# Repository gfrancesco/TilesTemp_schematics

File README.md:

# TilesTemp electronic schematics

In this repository are contained the Eagle schematic files for the TilesTemp temperature and humidity sensor.

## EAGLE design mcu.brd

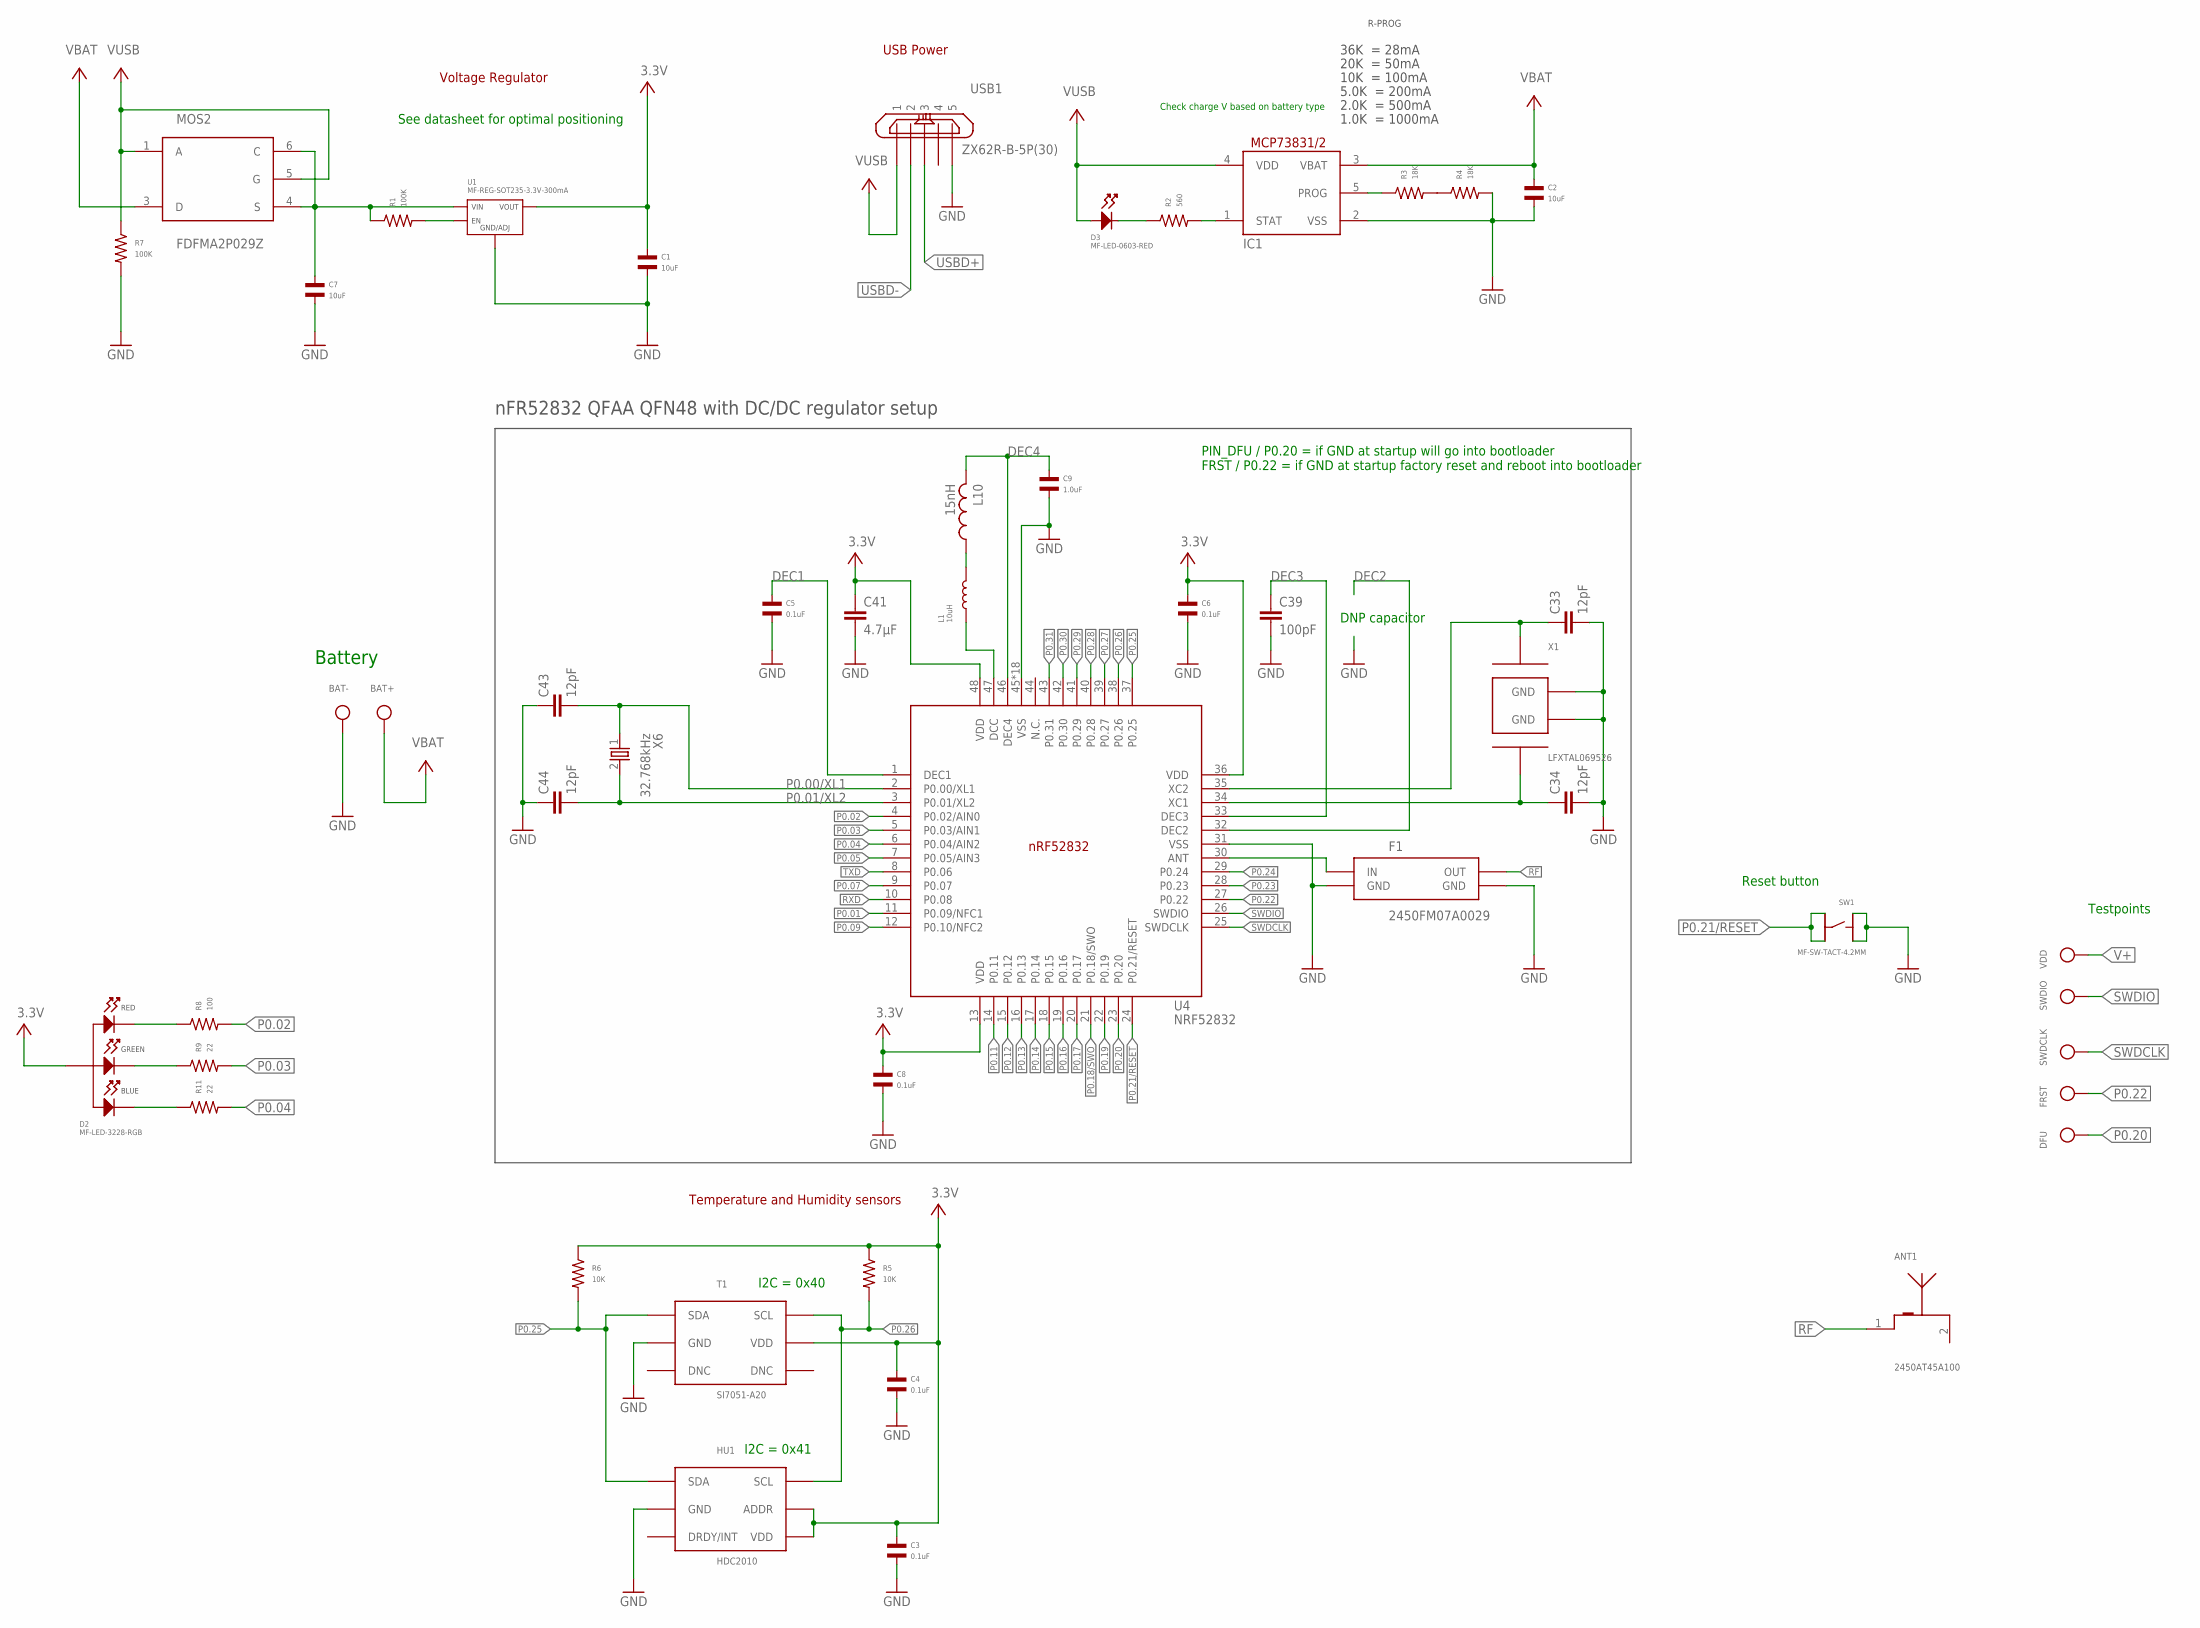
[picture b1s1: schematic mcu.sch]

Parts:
ANT1: 2450AT45A100; MPN 2450AT45A100E
BAT+: TESTPOINTROUND2MM; TESTPOINT_ROUND_2MM
BAT-: TESTPOINTROUND2MM; TESTPOINT_ROUND_2MM
C1, C2, C7: 10uF; C0603; MPN JMK107ABJ106KA-T
C3, C4, C5, C6, C8: 0.1uF; C0402; MPN MF-CAP-0402-0.1uF
C9: 1.0uF; C0603; MPN MF-CAP-0603-1uF
C33, C34, C43, C44: 12pF; RESC0402_N; MPN C0402C120J5GACTU
C39: 100pF; RESC0402_N; MPN GRM1555C1H101GA01D
C41: 4.7µF; RESC0603_N; MPN 06036D475KAT2A
D2: MF-LED-3228-RGB; PLCC4
D3: MF-LED-0603-RED; LED0603
DFU: TESTPOINTROUND2MM; TESTPOINT_ROUND_2MM
F1: 2450FM07A0029; 0402_RF; MPN 2450FM07A0029T
FRST: TESTPOINTROUND2MM; TESTPOINT_ROUND_2MM
HU1: HDC2010; DSBGA-6; MPN HDC2010YPAR
IC1: MCP73831/OT; SOT23-5L; MPN MCP73831T-2ACI/OT
L1: 10uH; L1210; MPN MF-IND-1210-10uH
L10: 15nH; RESC0402_N; MPN L-07C15NJV6T
MOS2: FDFMA2P029Z; MICROFET_2X2; MPN FDFMA2P029Z
R1, R7: 100K; R0402; MPN MF-RES-0402-100K
R2: 560; R0402; MPN MF-RES-0402-560
R3, R4: 18K; R0402; MPN MF-RES-0402-18K
R5, R6: 10K; R0402; MPN MF-RES-0402-10K
R8: 100; R0402; MPN MF-RES-0402-100
R9, R11: 22; R0402; MPN MF-RES-0402-22
SW1: MF-SW-TACT-4.2MM; TACT4.2MM
SWDCLK: TESTPOINTROUND2MM; TESTPOINT_ROUND_2MM
SWDIO: TESTPOINTROUND2MM; TESTPOINT_ROUND_2MM
T1: SI7051-A20; DFN-6; MPN SI7051-A20-IM
U1: MF-REG-SOT235-3.3V-300mA; SOT-23-5
U4: NRF52832; QFN40P600X600X90-48_N; MPN NRF52832-QFAA-R7
USB1: ZX62R-B-5P(30); MPN ZX62R-B-5P(30)
VDD: TESTPOINTROUND2MM; TESTPOINT_ROUND_2MM
X1: LFXTAL069526; 1612; MPN LFXTAL069526CUTT
X6: 32.768kHz; XTAL_3215_N; MPN LFXTAL009706REEL

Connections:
DEC1: C5.P$1, U4.1 (DEC1)
DEC2: U4.32 (DEC2)
DEC3: C39.1, U4.33 (DEC3)
DEC4: C9.P$1, L10.2, U4.46 (DEC4)
GND: BAT-.P$1, C1.P$2, C2.P$2, C3.P$2, C4.P$2, C5.P$2, C6.P$2, C7.P$2, C8.P$2, C9.P$2, C33.2, C34.2, C39.2, C41.2, C43.1, C44.1, F1.GND@2 (GND), F1.GND@4 (GND), HU1.C1 (GND), IC1.2 (VSS), R4.P$2, R7.P$2, SW1.P$1, SW1.P$2, T1.2 (GND), U1.P$2 (GND/ADJ), U4.31 (VSS), U4.45 (VSS), U4.PAD (VSS), U4.PAD@VIA01 (VSS), U4.PAD@VIA02 (VSS), U4.PAD@VIA03 (VSS), U4.PAD@VIA04 (VSS), U4.PAD@VIA05 (VSS), U4.PAD@VIA06 (VSS), U4.PAD@VIA07 (VSS), U4.PAD@VIA08 (VSS), U4.PAD@VIA09 (VSS), U4.PAD@VIA10 (VSS), U4.PAD@VIA11 (VSS), U4.PAD@VIA12 (VSS), U4.PAD@VIA13 (VSS), U4.PAD@VIA14 (VSS), U4.PAD@VIA15 (VSS), U4.PAD@VIA16 (VSS), USB1.5, X1.2 (GND), X1.4 (GND)
unnamed: R1.P$2, U1.P$3 (EN)
unnamed: IC1.1 (STAT), R2.P$2
unnamed: D3.CATHODE, R2.P$1
unnamed: D2.P$2 (CATHODE_RED), R8.P$1
unnamed: IC1.5 (PROG), R3.P$1
unnamed: D2.P$3 (CATHODE_GREEN), R9.P$1
unnamed: C33.1, U4.35 (XC2), X1.3 (2)
unnamed: L1.P$2, L10.1
unnamed: L1.P$1, U4.47 (DCC)
unnamed: C7.P$1, MOS2.4 (S), MOS2.6 (C), R1.P$1, U1.P$1 (VIN)
unnamed: R3.P$2, R4.P$1
unnamed: D2.P$4 (CATHODE_BLUE), R11.P$1
unnamed: F1.1 (IN), U4.30 (ANT)
P0.00/XL1: C43.2, U4.2 (P0.00/XL1), X6.1
P0.01: U4.11 (P0.09/NFC1)
P0.01/XL2: C44.2, U4.3 (P0.01/XL2), X6.2
P0.02: R8.P$2, U4.4 (P0.02/AIN0)
P0.03: R9.P$2, U4.5 (P0.03/AIN1)
P0.04: R11.P$2, U4.6 (P0.04/AIN2)
P0.05: U4.7 (P0.05/AIN3)
P0.07: U4.9 (P0.07)
P0.09: U4.12 (P0.10/NFC2)
P0.11: U4.14 (P0.11)
P0.12: U4.15 (P0.12)
P0.13: U4.16 (P0.13)
P0.14: U4.17 (P0.14)
P0.15: U4.18 (P0.15)
P0.16: U4.19 (P0.16)
P0.17: U4.20 (P0.17)
P0.18/SWO: U4.21 (P0.18/SWO)
P0.19: U4.22 (P0.19)
P0.20: DFU.P$1, U4.23 (P0.20)
P0.21/RESET: SW1.P$3, SW1.P$4, U4.24 (P0.21/RESET)
P0.22: FRST.P$1, U4.27 (P0.22)
P0.23: U4.28 (P0.23)
P0.24: U4.29 (P0.24)
P0.25: HU1.A2 (SDA), R6.P$2, T1.1 (SDA), U4.37 (P0.25)
P0.26: HU1.B2 (SCL), R5.P$2, T1.6 (SCL), U4.38 (P0.26)
P0.27: U4.39 (P0.27)
P0.28: U4.40 (P0.28)
P0.29: U4.41 (P0.29)
P0.30: U4.42 (P0.30)
P0.31: U4.43 (P0.31)
RF: ANT1.1, F1.3 (OUT)
RXD: U4.10 (P0.08)
SWDCLK: SWDCLK.P$1, U4.25 (SWDCLK)
SWDIO: SWDIO.P$1, U4.26 (SWDIO)
TXD: U4.8 (P0.06)
USBD+: USB1.3
USBD-: USB1.2
V+: C1.P$1, C3.P$1, C4.P$1, C6.P$1, C8.P$1, C41.1, D2.P$1 (ANODE), HU1.A1 (VDD), HU1.B1 (ADDR), R5.P$1, R6.P$1, T1.5 (VDD), U1.P$5 (VOUT), U4.13 (VDD), U4.36 (VDD), U4.48 (VDD), VDD.P$1
VBAT: BAT+.P$1, C2.P$1, IC1.3 (VBAT), MOS2.3 (D)
VUSB: D3.ANODE, IC1.4 (VDD), MOS2.1 (A), MOS2.5 (G), R7.P$1, USB1.1
X3: C34.1, U4.34 (XC1), X1.1

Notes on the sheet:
nFR52832 QFAA QFN48 with DC/DC regulator setup
Voltage Regulator
USB Power
See datasheet for optimal positioning
PIN_DFU / P0.20 = if GND at startup will go into bootloader FRST / P0.22 = if GND at startup factory reset and reboot into bootloader
Reset button
Testpoints
10K = 100mA
5.0K = 200mA
2.0K = 500mA
1.0K = 1000mA
20K = 50mA
R-PROG
Battery
Check charge V based on battery type
Temperature and Humidity sensors
I2C = 0x40
I2C = 0x41
36K = 28mA
DNP capacitor

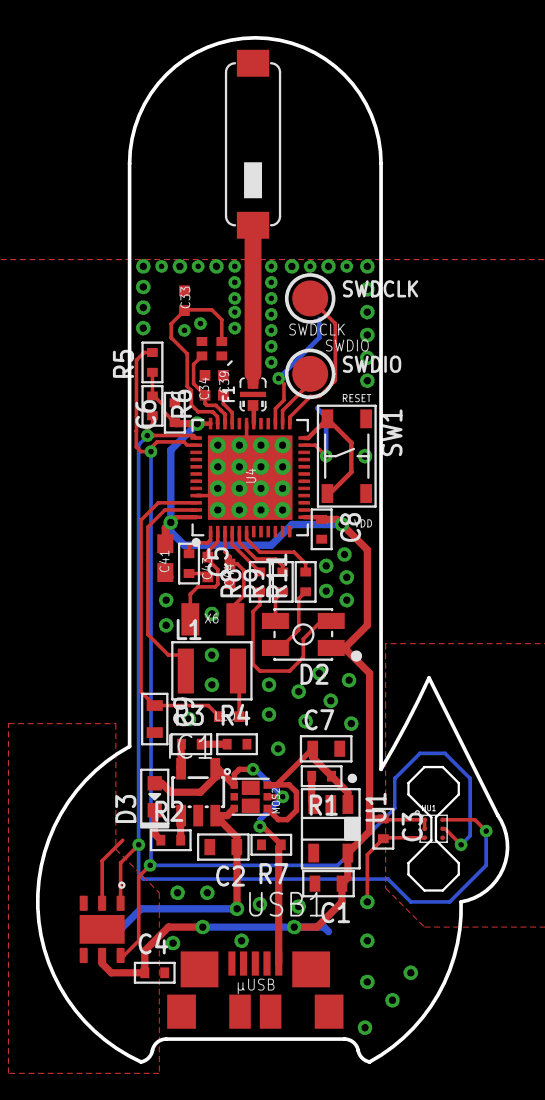
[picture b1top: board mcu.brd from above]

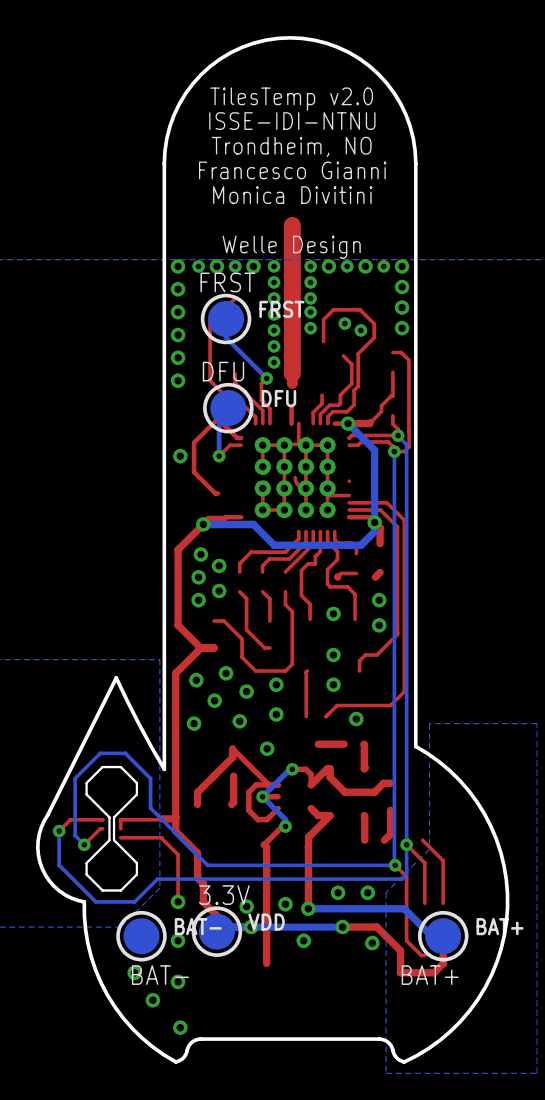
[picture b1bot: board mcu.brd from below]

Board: 2 copper layers, 26.1 x 56.9 mm, 48 parts (5 on the bottom side), 34 nets.

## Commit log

2017-11-13 First commit.
2017-12-23 ADD: component and library
2018-01-02 ADD: microbuilder lib
2018-01-02 UPD: schematics
2018-01-04 UPD: schem
2018-01-04 UPD: leds
2018-01-05 UPD: board
2018-01-05 UPD: wiring
2018-01-08 UPD: finished wiring
2018-01-08 UPD: testpoints schematic
2018-01-08 UPD: names
2018-01-08 UPD: usb position
2018-01-09 UPD: coplanar waveguide
2018-01-10 UPD: board, and RF line
2018-01-12 UPD: feed
2018-01-12 UPD: battery
2018-01-13 UPD: finished before moving left area
2018-01-13 UPD: finishied version to macrofab
2018-01-14 UPD: minor
2018-02-22 FIX: txd, rxd lines, usb. UPD: testpoints.
2018-02-22 FIX: usb connections
2018-02-26 UPD readme
2018-03-01 UPD: v2 wiring complete
2018-03-04 ADD: microfet package
2018-03-05 UPD: design and components
2018-03-05 UPD: finished design for v2, submitted to macrofab

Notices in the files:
parts and their libraries:
microbuilder: This work is placed in the public domain, and may be freely used for commercial and non-commercial work with the following conditions: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
